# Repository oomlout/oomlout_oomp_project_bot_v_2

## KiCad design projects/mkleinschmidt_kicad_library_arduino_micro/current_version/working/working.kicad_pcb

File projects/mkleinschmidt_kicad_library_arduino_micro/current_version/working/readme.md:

# kicad_library
 
## summary 
* id: mkleinschmidt_kicad_library_arduino_micro
* user: mkleinschmidt
* name: kicad_library
* board: arduino_micro
* repo: https://github.com/mkleinschmidt/kicad-library
* src_file_repo_kicad_pcb: template/Arduino_Micro/Arduino_Micro.kicad_pcb
* src_file_repo_kicad_pcb_link: https://github.com/mkleinschmidt/kicad-library/tree/master/template/Arduino_Micro/Arduino_Micro.kicad_pcb

* src_file_repo_sch: template/Arduino_Micro/Arduino_Micro.sch
* src_file_repo_sch_link: https://github.com/mkleinschmidt/kicad-library/tree/master/template/Arduino_Micro/Arduino_Micro.sch
* full details link: https://github.com/oomlout/oomlout_oomp_project_bot_v_2/tree/main/projects/mkleinschmidt_kicad_library_arduino_micro/current_version/working

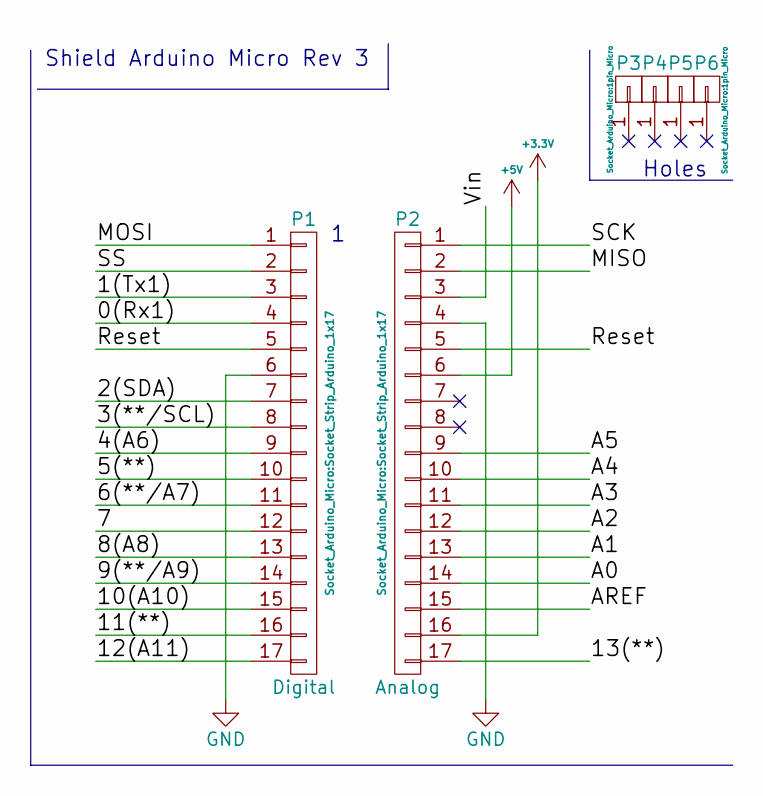
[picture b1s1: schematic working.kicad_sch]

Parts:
P1: Digital; Socket_Strip_Arduino_1x17
P2: Analog; Socket_Strip_Arduino_1x17
P3, P4, P5, P6: CONN_01X01; 1pin_Micro

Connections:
+3V3: P2.16
+5V: P2.6
/0(Rx1): P1.4
/1(Tx1): P1.3
/2(SDA): P1.7
/3(**/SCL): P1.8
/4(A6): P1.9
/5(**): P1.10
/6(**/A7): P1.11
/7: P1.12
/8(A8): P1.13
/9(**/A9): P1.14
/10(A10): P1.15
/11(**): P1.16
/12(A11): P1.17
/13(**): P2.17
/A0: P2.14
/A1: P2.13
/A2: P2.12
/A3: P2.11
/A4: P2.10
/A5: P2.9
/AREF: P2.15
/MISO: P2.2
/MOSI: P1.1
/Reset: P1.5, P2.5
/SCK: P2.1
/SS: P1.2
/Vin: P2.3
GND: P1.6, P2.4

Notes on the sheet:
Shield Arduino Micro Rev 3
Holes

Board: 2 copper layers, 6 parts (0 on the bottom side), 2 nets, no tracks yet.

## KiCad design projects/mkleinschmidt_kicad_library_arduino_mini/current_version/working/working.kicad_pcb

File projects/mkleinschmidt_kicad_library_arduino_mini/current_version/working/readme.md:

# kicad_library
 
## summary 
* id: mkleinschmidt_kicad_library_arduino_mini
* user: mkleinschmidt
* name: kicad_library
* board: arduino_mini
* repo: https://github.com/mkleinschmidt/kicad-library
* src_file_repo_kicad_pcb: template/Arduino_Mini/Arduino_Mini.kicad_pcb
* src_file_repo_kicad_pcb_link: https://github.com/mkleinschmidt/kicad-library/tree/master/template/Arduino_Mini/Arduino_Mini.kicad_pcb

* src_file_repo_sch: template/Arduino_Mini/Arduino_Mini.sch
* src_file_repo_sch_link: https://github.com/mkleinschmidt/kicad-library/tree/master/template/Arduino_Mini/Arduino_Mini.sch
* full details link: https://github.com/oomlout/oomlout_oomp_project_bot_v_2/tree/main/projects/mkleinschmidt_kicad_library_arduino_mini/current_version/working

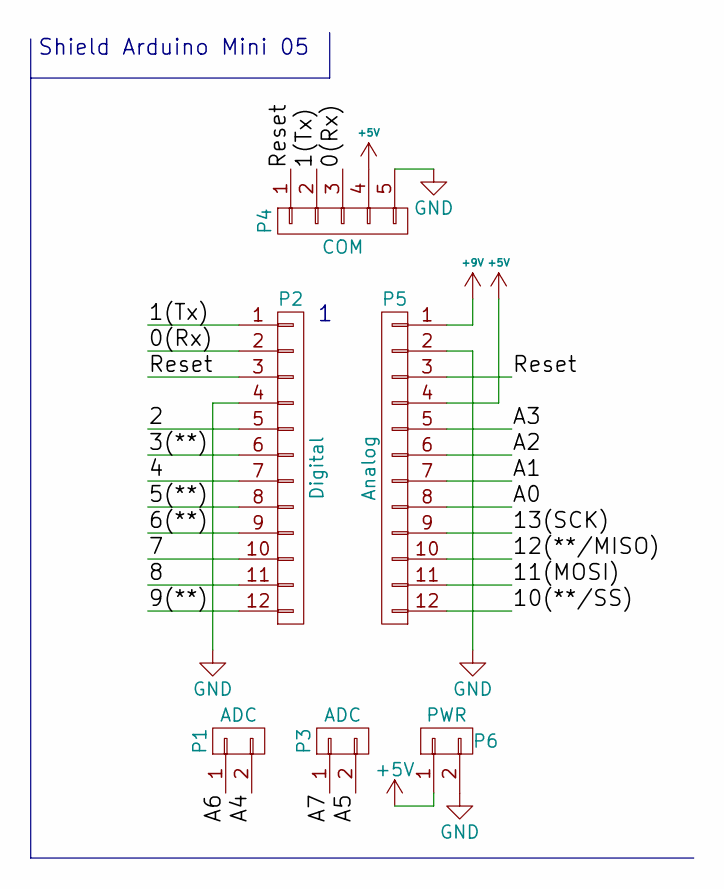
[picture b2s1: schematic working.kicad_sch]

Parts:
P1, P3: ADC; Socket_Strip_Arduino_1x02
P2: Digital; Socket_Strip_Arduino_1x12
P4: COM; Socket_Strip_Arduino_1x05
P5: Analog; Socket_Strip_Arduino_1x12
P6: PWR; Socket_Strip_Arduino_1x02

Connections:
+5V: P4.4, P5.4, P6.1
+9V: P5.1
/0(Rx): P2.2, P4.3
/1(Tx): P2.1, P4.2
/2: P2.5
/3(**): P2.6
/4: P2.7
/5(**): P2.8
/6(**): P2.9
/7: P2.10
/8: P2.11
/9(**): P2.12
/10(**/SS): P5.12
/11(MOSI): P5.11
/12(**/MISO): P5.10
/13(SCK): P5.9
/A0: P5.8
/A1: P5.7
/A2: P5.6
/A3: P5.5
/A4: P1.2
/A5: P3.2
/A6: P1.1
/A7: P3.1
/Reset: P2.3, P4.1, P5.3
GND: P2.4, P4.5, P5.2, P6.2

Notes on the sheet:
Shield Arduino Mini 05

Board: 2 copper layers, 6 parts (0 on the bottom side), 5 nets, no tracks yet.

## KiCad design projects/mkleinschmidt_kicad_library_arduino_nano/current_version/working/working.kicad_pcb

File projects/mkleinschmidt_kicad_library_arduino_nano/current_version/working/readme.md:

# kicad_library
 
## summary 
* id: mkleinschmidt_kicad_library_arduino_nano
* user: mkleinschmidt
* name: kicad_library
* board: arduino_nano
* repo: https://github.com/mkleinschmidt/kicad-library
* src_file_repo_kicad_pcb: template/Arduino_Nano/Arduino_Nano.kicad_pcb
* src_file_repo_kicad_pcb_link: https://github.com/mkleinschmidt/kicad-library/tree/master/template/Arduino_Nano/Arduino_Nano.kicad_pcb

* src_file_repo_sch: template/Arduino_Nano/Arduino_Nano.sch
* src_file_repo_sch_link: https://github.com/mkleinschmidt/kicad-library/tree/master/template/Arduino_Nano/Arduino_Nano.sch
* full details link: https://github.com/oomlout/oomlout_oomp_project_bot_v_2/tree/main/projects/mkleinschmidt_kicad_library_arduino_nano/current_version/working

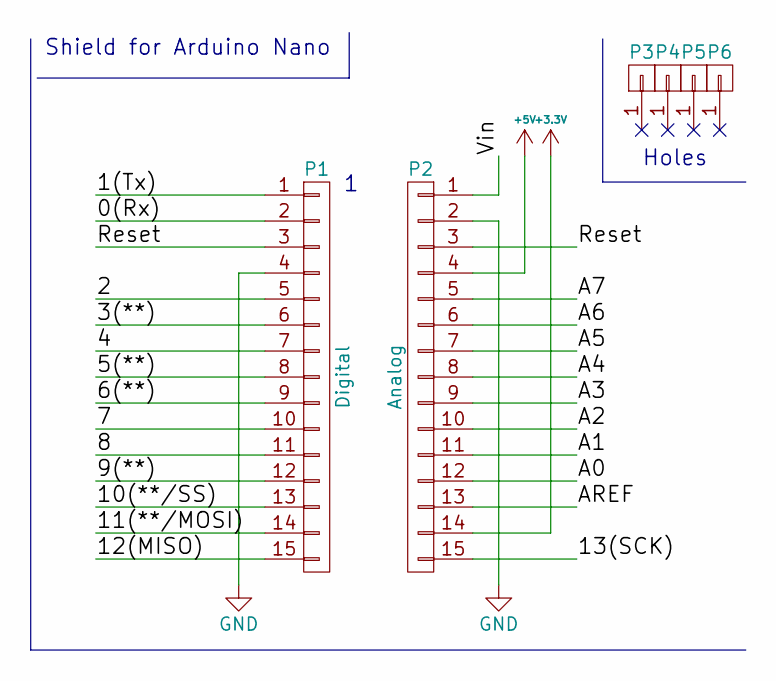
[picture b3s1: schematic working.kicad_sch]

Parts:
P1: Digital; Socket_Strip_Arduino_1x15
P2: Analog; Socket_Strip_Arduino_1x15
P3, P4, P5, P6: CONN_01X01; 1pin_Nano

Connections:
+3V3: P2.14
+5V: P2.4
/0(Rx): P1.2
/1(Tx): P1.1
/2: P1.5
/3(**): P1.6
/4: P1.7
/5(**): P1.8
/6(**): P1.9
/7: P1.10
/8: P1.11
/9(**): P1.12
/10(**/SS): P1.13
/11(**/MOSI): P1.14
/12(MISO): P1.15
/13(SCK): P2.15
/A0: P2.12
/A1: P2.11
/A2: P2.10
/A3: P2.9
/A4: P2.8
/A5: P2.7
/A6: P2.6
/A7: P2.5
/AREF: P2.13
/Reset: P1.3, P2.3
/Vin: P2.1
GND: P1.4, P2.2

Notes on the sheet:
Shield for Arduino Nano
Holes

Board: 2 copper layers, 6 parts (0 on the bottom side), 2 nets, no tracks yet.

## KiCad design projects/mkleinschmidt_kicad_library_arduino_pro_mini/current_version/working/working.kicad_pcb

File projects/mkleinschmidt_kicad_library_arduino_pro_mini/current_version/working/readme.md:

# kicad_library
 
## summary 
* id: mkleinschmidt_kicad_library_arduino_pro_mini
* user: mkleinschmidt
* name: kicad_library
* board: arduino_pro_mini
* repo: https://github.com/mkleinschmidt/kicad-library
* src_file_repo_kicad_pcb: template/Arduino_Pro_Mini/Arduino_Pro_Mini.kicad_pcb
* src_file_repo_kicad_pcb_link: https://github.com/mkleinschmidt/kicad-library/tree/master/template/Arduino_Pro_Mini/Arduino_Pro_Mini.kicad_pcb

* src_file_repo_sch: template/Arduino_Pro_Mini/Arduino_Pro_Mini.sch
* src_file_repo_sch_link: https://github.com/mkleinschmidt/kicad-library/tree/master/template/Arduino_Pro_Mini/Arduino_Pro_Mini.sch
* full details link: https://github.com/oomlout/oomlout_oomp_project_bot_v_2/tree/main/projects/mkleinschmidt_kicad_library_arduino_pro_mini/current_version/working

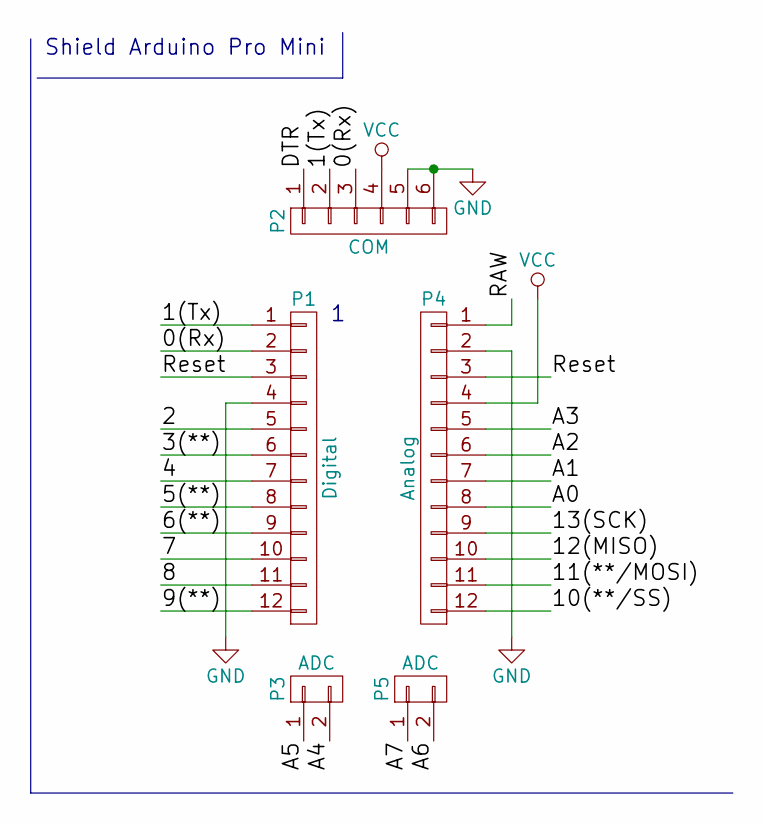
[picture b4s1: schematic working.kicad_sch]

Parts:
P1: Digital; Socket_Strip_Arduino_1x12
P2: COM; Socket_Strip_Arduino_1x06
P3, P5: ADC; Socket_Strip_Arduino_1x02
P4: Analog; Socket_Strip_Arduino_1x12

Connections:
/0(Rx): P1.2, P2.3
/1(Tx): P1.1, P2.2
/2: P1.5
/3(**): P1.6
/4: P1.7
/5(**): P1.8
/6(**): P1.9
/7: P1.10
/8: P1.11
/9(**): P1.12
/10(**/SS): P4.12
/11(**/MOSI): P4.11
/12(MISO): P4.10
/13(SCK): P4.9
/A0: P4.8
/A1: P4.7
/A2: P4.6
/A3: P4.5
/A4: P3.2
/A5: P3.1
/A6: P5.2
/A7: P5.1
/DTR: P2.1
/RAW: P4.1
/Reset: P1.3, P4.3
GND: P1.4, P2.5, P2.6, P4.2
VCC: P2.4, P4.4

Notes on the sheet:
Shield Arduino Pro Mini

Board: 2 copper layers, 5 parts (0 on the bottom side), 5 nets, no tracks yet.
